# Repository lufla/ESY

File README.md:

# ESY git repository

This repository contains the digital appendix of the ESY project winter term 2025/26.

## Created files:

| Folder | Description |
|--------|-------------|
|[DE10-Nano-CAM](./DE10-Nano-CAM/) | Base board hardware files |
|[firmware/project](./firmware/project/) | Final project files|
|[firmware/hw_simple](./firmware/hw_simple/) | Description of software installation and the complete workflow to create the bitstream |
|[mechanical-design](./mechanical-design/) | 3D files for the mechanical case|
|[Doc](./Doc/) | Source file for the documentation |
|[firmware/hw_test](./firmware/hw_test/) | LED blinky used for all hardware testing |

## Files, that this project is based upon:

| Folder | Description |
|--------|-------------|
|[GateMateCode_Krause](./GateMateCode_Krause/) | Original codebase by Sven Krause adapted to the hardware of this project |
|[ulx5m-gs](./ulx5m-gs/) | SOM board hardware files |
|[Krause_Thesis.pdf](./Krause_Thesis.pdf) | Masters thesis by Sven Krause |

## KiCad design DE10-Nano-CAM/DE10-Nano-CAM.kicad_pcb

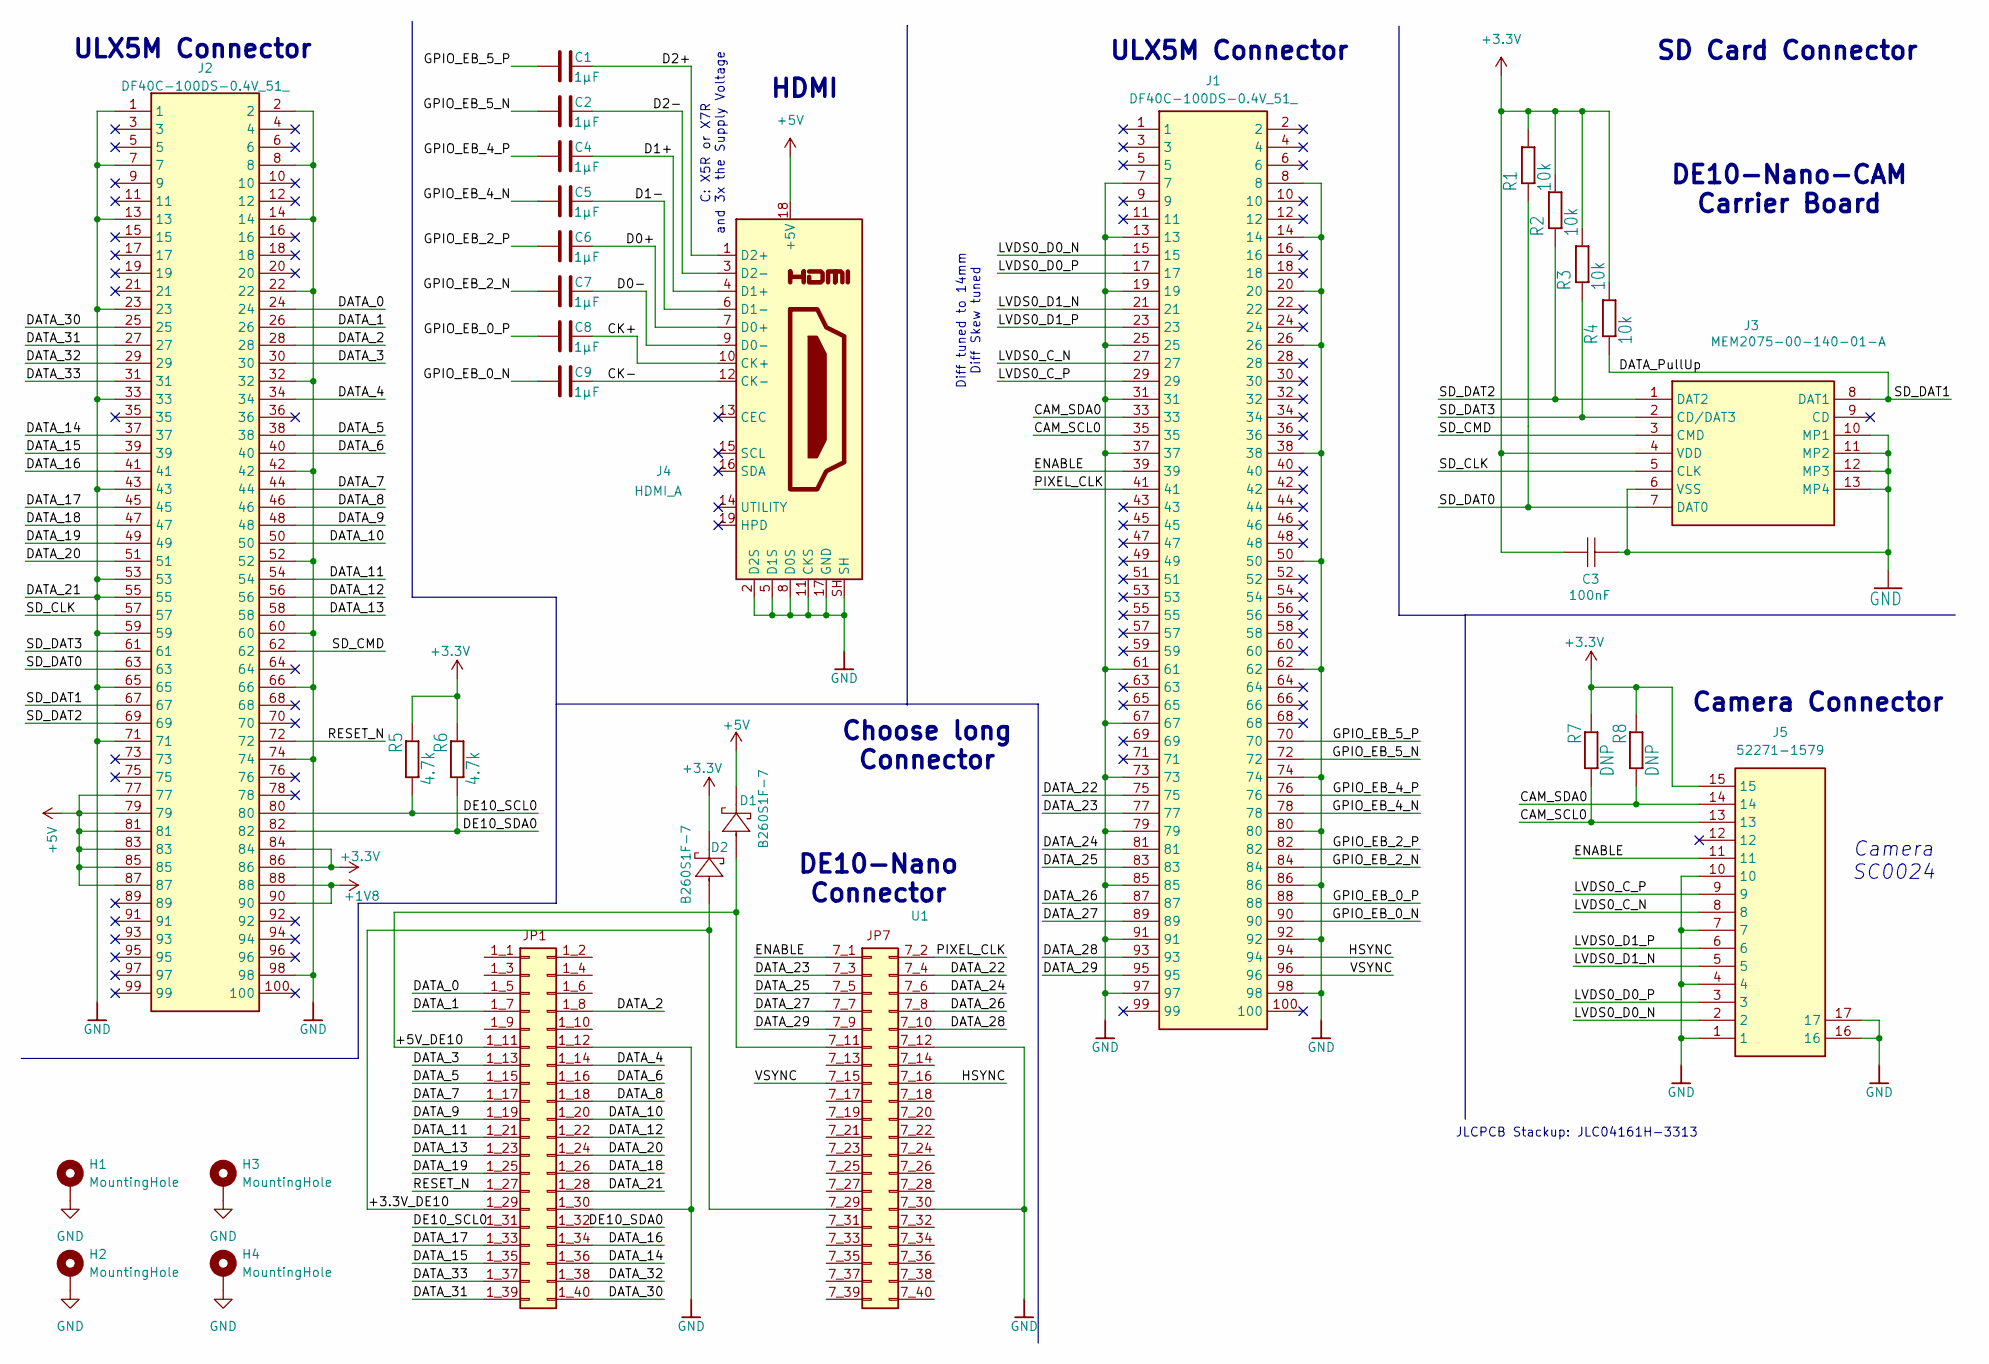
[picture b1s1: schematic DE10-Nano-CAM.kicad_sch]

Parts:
C1, C2, C4, C5, C6, C7, C8, C9: 1µF; C_0402_1005Metric
C3: 100nF; C_0603_1608Metric
D1, D2: B260S1F-7; D_0805_2012Metric; MANUFACTURER_PART_NUMBER B260S1F-7; DIGI-KEY_PART_NUMBER_1 B260S1F-7DITR-ND
H1, H2, H3, H4: MountingHole; MountingHole_2.7mm_M2.5_DIN965_Pad
J1, J2: DF40C-100DS-0.4V_51_; DF40C100DS04V51; Mouser Part Number 798-DF40C100DS0.4V51
J3: MEM2075-00-140-01-A; MEM20750014001A; Mouser Part Number 640-MEM20750014001A
J4: HDMI_A; HDMI_A_Amphenol_10029449-x01xLF_Horizontal
J5: 52271-1579; 522711579; Mouser Part Number 538-52271-1579
R1, R2, R3, R4: 10k; R_0402_1005Metric
R5, R6: 4.7k; R_0603_1608Metric
R7, R8: DNP; R_0603_1608Metric
U1: DE10-Nano

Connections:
+1V8: J2.88, J2.90
+3.3V: C3.2, D2.1, J2.84, J2.86, J3.4 (VDD), J5.15, R1.2, R2.2, R3.2, R4.2, R5.2, R6.2, R7.2, R8.2
+5V: D1.1, J2.77, J2.79, J2.81, J2.83, J2.85, J2.87, J4.18 (+5V)
/+3.3V_DE10: D2.2, U1.1_29, U1.7_29
/+5V_DE10: D1.2, U1.1_11, U1.7_11
/CAM_SCL0: J1.35, J5.13, R7.1
/CAM_SDA0: J1.33, J5.14, R8.1
/CK+: C8.2, J4.10 (CK+)
/CK-: C9.2, J4.12 (CK-)
/D0+: C6.2, J4.7 (D0+)
/D0-: C7.2, J4.9 (D0-)
/D1+: C4.2, J4.4 (D1+)
/D1-: C5.2, J4.6 (D1-)
/D2+: C1.2, J4.1 (D2+)
/D2-: C2.2, J4.3 (D2-)
/DATA_0: J2.24, U1.1_5
/DATA_1: J2.26, U1.1_7
/DATA_2: J2.28, U1.1_8
/DATA_3: J2.30, U1.1_13
/DATA_4: J2.34, U1.1_14
/DATA_5: J2.38, U1.1_15
/DATA_6: J2.40, U1.1_16
/DATA_7: J2.44, U1.1_17
/DATA_8: J2.46, U1.1_18
/DATA_9: J2.48, U1.1_19
/DATA_10: J2.50, U1.1_20
/DATA_11: J2.54, U1.1_21
/DATA_12: J2.56, U1.1_22
/DATA_13: J2.58, U1.1_23
/DATA_14: J2.37, U1.1_36
/DATA_15: J2.39, U1.1_35
/DATA_16: J2.41, U1.1_34
/DATA_17: J2.45, U1.1_33
/DATA_18: J2.47, U1.1_26
/DATA_19: J2.49, U1.1_25
/DATA_20: J2.51, U1.1_24
/DATA_22: J1.75, U1.7_4
/DATA_23: J1.77, U1.7_3
/DATA_24: J1.81, U1.7_6
/DATA_25: J1.83, U1.7_5
/DATA_26: J1.87, U1.7_8
/DATA_27: J1.89, U1.7_7
/DATA_28: J1.93, U1.7_10
/DATA_29: J1.95, U1.7_9
/DATA_30: J2.25, U1.1_40
/DATA_31: J2.27, U1.1_39
/DATA_32: J2.29, U1.1_38
/DATA_33: J2.31, U1.1_37
/DATA_PullUp: J2.67, J3.8 (DAT1), R4.1
/DE10_SCL0: J2.80, R5.1, U1.1_31
/DE10_SDA0: J2.82, R6.1, U1.1_32
/ENABLE: J1.39, J5.11, U1.7_1
/GPIO_EB_0_N: C9.1, J1.90
/GPIO_EB_0_P: C8.1, J1.88
/GPIO_EB_2_N: C7.1, J1.84
/GPIO_EB_2_P: C6.1, J1.82
/GPIO_EB_4_N: C5.1, J1.78
/GPIO_EB_4_P: C4.1, J1.76
/GPIO_EB_5_N: C2.1, J1.72
/GPIO_EB_5_P: C1.1, J1.70
/HSYNC: J1.94, U1.7_16
/LVDS0_C_N: J1.27, J5.8
/LVDS0_C_P: J1.29, J5.9
/LVDS0_D0_N: J1.15, J5.2
/LVDS0_D0_P: J1.17, J5.3
/LVDS0_D1_N: J1.21, J5.5
/LVDS0_D1_P: J1.23, J5.6
/PIXEL_CLK: J1.41, U1.7_2
/RESET_N: J2.72, U1.1_27
/SD_CLK: J2.57, J3.5 (CLK)
/SD_CMD: J2.62, J3.3 (CMD)
/SD_DAT0: J2.63, J3.7 (DAT0), R1.1
/SD_DAT2: J2.69, J3.1 (DAT2), R2.1
/SD_DAT3: J2.61, J3.2 (CD/DAT3), R3.1
/VSYNC: J1.96, U1.7_15
GND: C3.1, H1.1, H2.1, H3.1, H4.1, J1.7, J1.8, J1.13, J1.14, J1.19, J1.20, J1.25, J1.26, J1.31, J1.37, J1.38, J1.50, J1.61, J1.62, J1.67, J1.73, J1.74, J1.79, J1.80, J1.85, J1.86, J1.91, J1.92, J1.97, J1.98, J2.1, J2.2, J2.7, J2.8, J2.13, J2.14, J2.22, J2.23, J2.32, J2.33, J2.42, J2.43, J2.52, J2.53, J2.55, J2.59, J2.60, J2.65, J2.66, J2.71, J2.74, J2.98, J3.6 (VSS), J3.10 (MP1), J3.11 (MP2), J3.12 (MP3), J3.13 (MP4), J4.2 (D2S), J4.5 (D1S), J4.8 (D0S), J4.11 (CKS), J4.17 (GND), J4.SH, J5.1, J5.4, J5.7, J5.10, J5.16, J5.17, U1.1_12, U1.1_28, U1.1_30, U1.7_12, U1.7_30

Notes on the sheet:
DE10-Nano-CAM Carrier Board
Camera SC0024
C: X5R or X7R and 3x the Supply Voltage
Camera Connector
Choose long Connector
DE10-Nano Connector
JLCPCB Stackup: JLC04161H-3313
ULX5M Connector
SD Card Connector
HDMI
Diff tuned to 14mm Diff Skew tuned

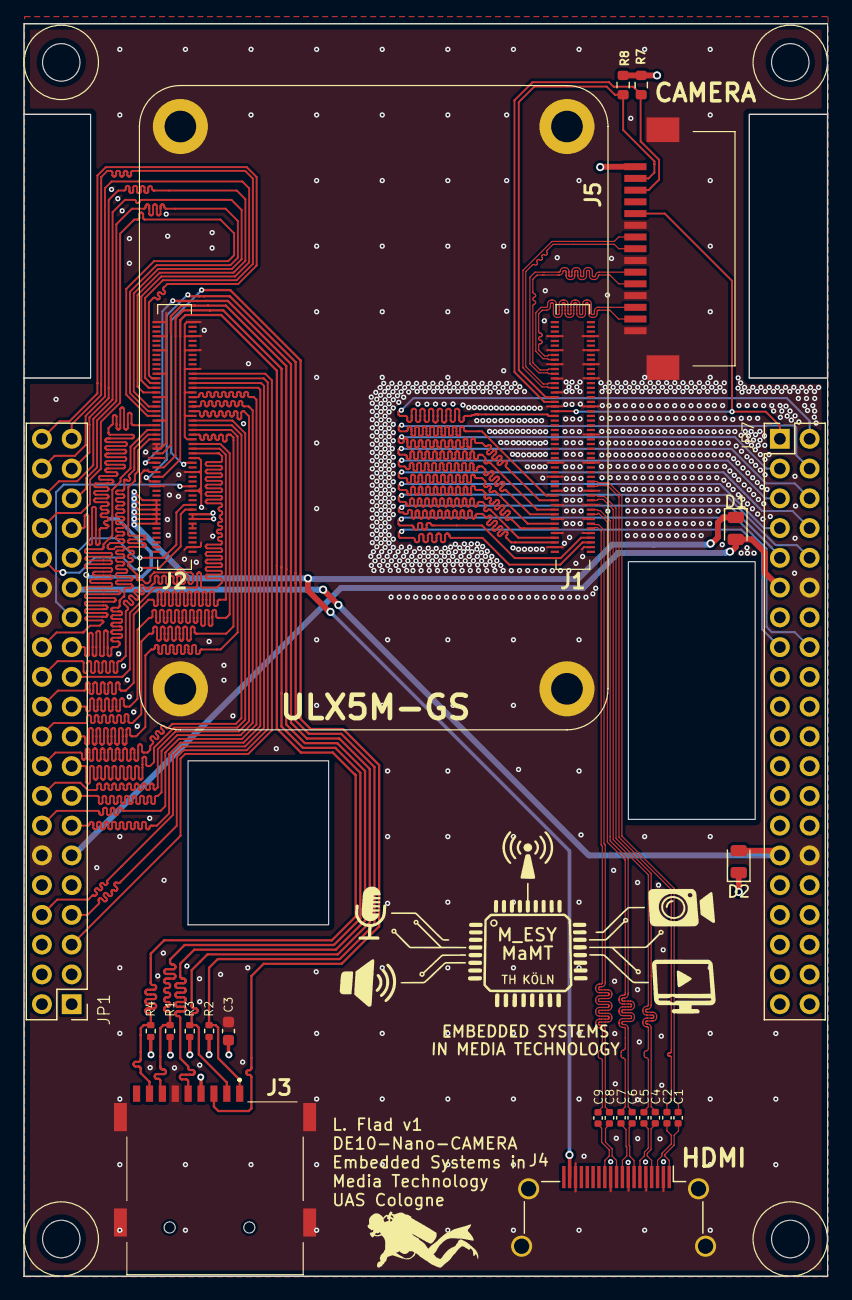
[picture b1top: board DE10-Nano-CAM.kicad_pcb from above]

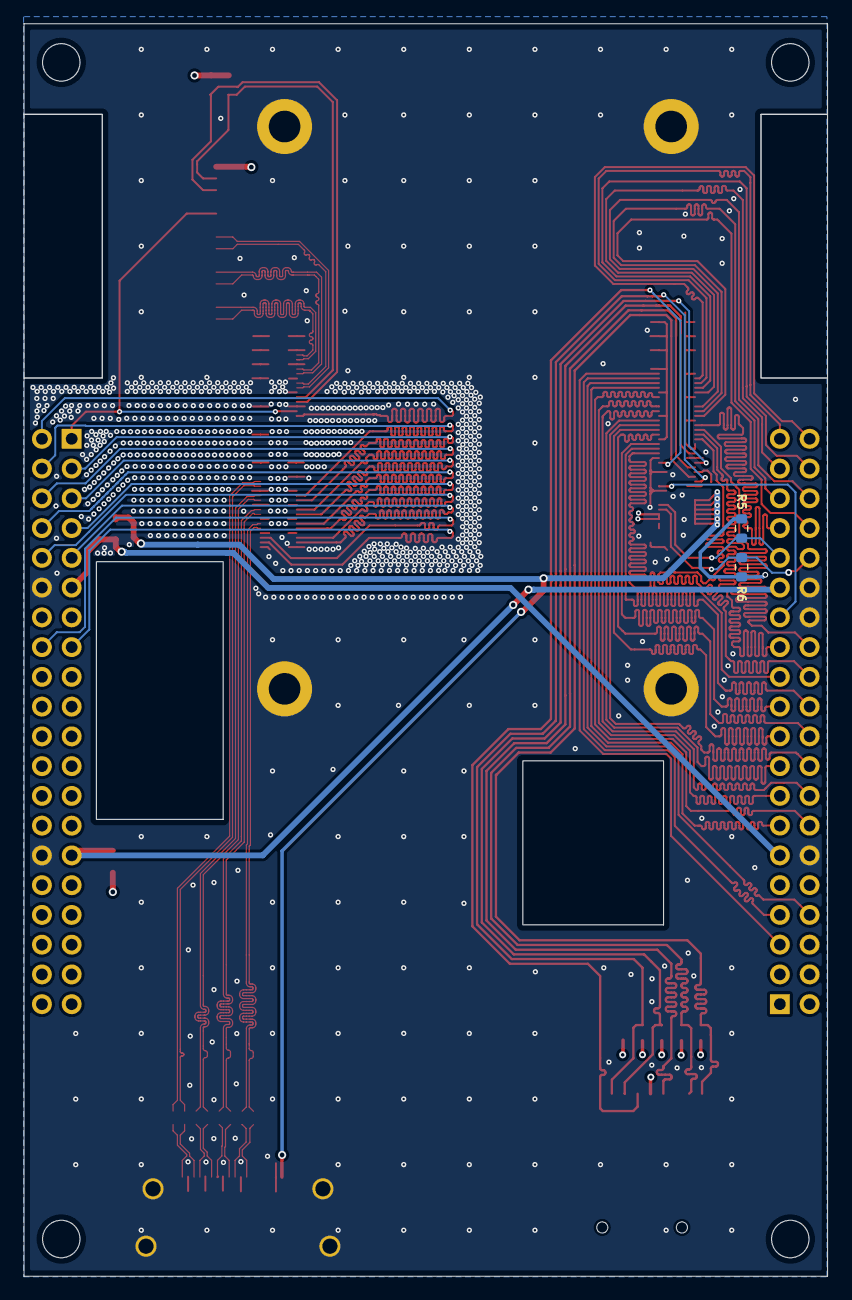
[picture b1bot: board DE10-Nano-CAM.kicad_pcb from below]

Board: 4 copper layers, 68.6 x 106.9 mm, 29 parts (2 on the bottom side), 76 nets.

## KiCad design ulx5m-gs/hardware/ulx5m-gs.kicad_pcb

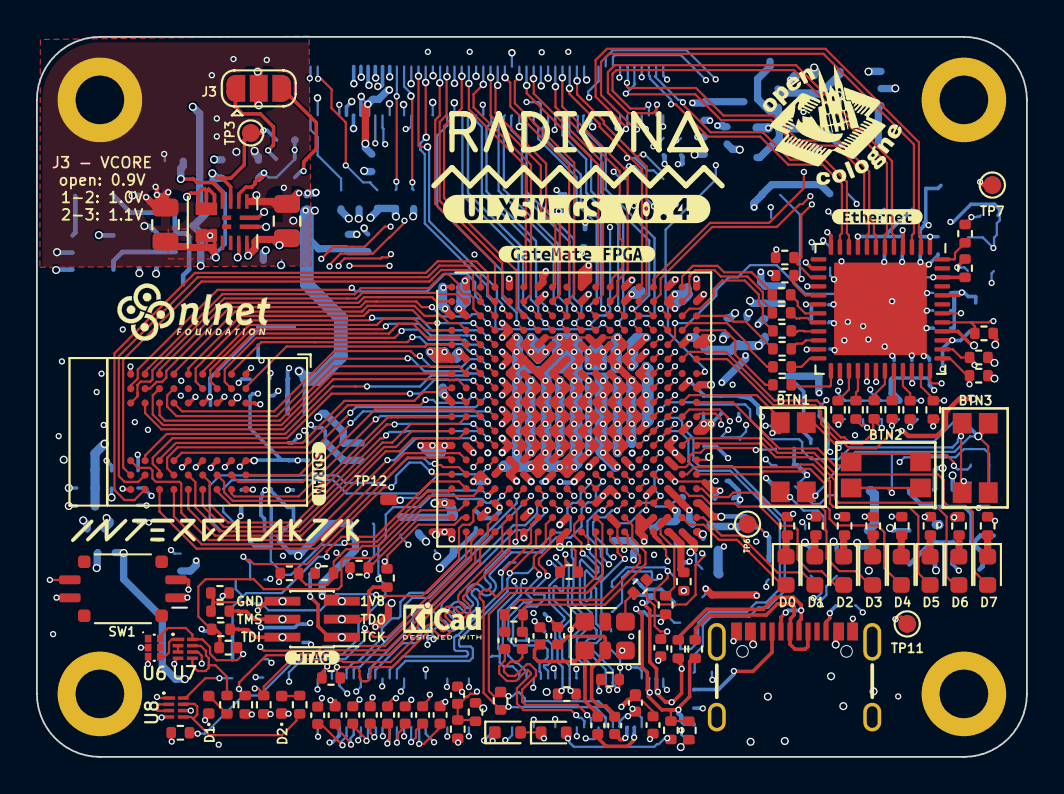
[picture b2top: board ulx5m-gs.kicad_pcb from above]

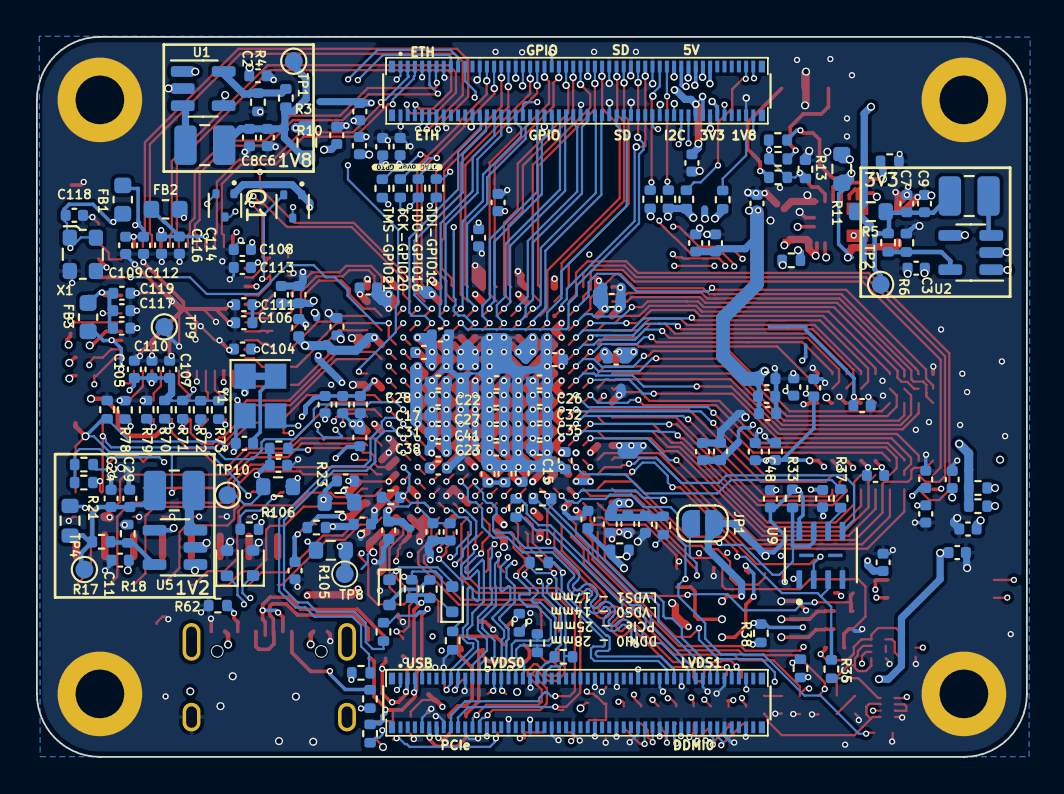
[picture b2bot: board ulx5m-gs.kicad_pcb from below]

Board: 6 copper layers, 55.0 x 40.0 mm, 310 parts (192 on the bottom side), 275 nets.

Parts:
BTN1, BTN2, BTN3: SW_Push; Switch_EVPAA
C1, C10: 22u; C_0805_2012Metric
C2, C3, C11, C115: 4u7; C_0402_1005Metric
C4, C15, C18, C23, C28, C32, C35, C38, C41, C110, C111, C113, C119, C126: 10n; C_0402_1005Metric
C6, C7, C24, C104, C105, C109, C114: 10u; C_0402_1005Metric
C8, C9, C29: 1u; C_0402_1005Metric
C13, C16, C21, C26, C36, C44, C51, C54, C75, C78, C86, C90, C94, C100, C122, C123, C131: 2u2; C_0402_1005Metric
C14, C17, C22, C27, C31, C34, C37, C40, C42, C45, C47, C48, C49, C52, C55, C56, C57, C76, C79, C80, C88, C89, C92, C93, C96, C97, C102, C103, C106, C107, C108, C112, C116, C117, C118, C127, C128, C129, C130, C132, C133, C134, C135, C136, C137, C138: 100n; C_0402_1005Metric
C33, C59, C60, C61, C62, C63, C64, C65, C66, C87, C91, C95, C120, C121: 220n; C_0402_1005Metric
C39, C43, C50, C53, C58, C77, C98, C124, C125: 22u; C_0402_1005Metric
C85: 2.2uF; C_0402_1005Metric
C99, C101, C140, C141: 22nF; C_0402_1005Metric
D1: green; D_0402_1005Metric
D2: red; D_0402_1005Metric
D3, D4: 3.6V; D_SOD-523
D5, D6, D7, D8: 1N914; D_SOD-523
D9, D10, D11, D12, D13, D14, D15, D16: LED; LED_0603_1608Metric
FB1, FB2, FB3: BLM18PG121SN1D; L_0603_1608Metric
H1, H2, H3, H4: MountingHole; MountingHole_2.7mm_M2.5_DIN965_Pad
J1, J2: DF40C-100DP-0.4V_51_; HRS_DF40C-100DP-0.4V_51_
J3: Vcore_sel; SolderJumper-3_P1.3mm_Open_RoundedPad1.0x1.5mm
J4: JTAG; PinHeader_2x03_P1.00mm_Vertical_SMD
J5: USB_C_Receptacle; USB-C_16
JP1: POR_EN; SolderJumper-2_P1.3mm_Open_RoundedPad1.0x1.5mm
L1, L2, L3: DFE322512F-2R2M=P2; L_1008_2520Metric
LoGo_opencologne: MountingHole; open_cologne_small
Q1, Q2: BSS138; SOT-523
R1, R4, R5, R143: 100k; R_0402_1005Metric
R2: 51k; R_0402_1005Metric
R3, R17, R18: 200k; R_0402_1005Metric
R6: 22k; R_0402_1005Metric
R7, R8, R116, R141, R142: 0R; R_0402_1005Metric
R9, R107, R108, R110, R112, R113, R115: dnp; R_0402_1005Metric
R10, R11, R13, R21: 0R; R_0603_1608Metric
R12: 40k; R_0402_1005Metric
R14: 120k; R_0402_1005Metric
R15: 20k; R_0402_1005Metric
R16: 60k; R_0402_1005Metric
R23, R105, R106: 1R; R_0603_1608Metric
R24, R25, R27, R29, R30, R111, R128, R134, R138, R139, R147, R148, R149, R150: 10k; R_0402_1005Metric
R31, R32: 200R; R_0402_1005Metric
R33, R34, R35, R36, R38, R39, R66, R67, R70, R71, R72, R73, R78, R79, R84, R85, R96: 4k7; R_0402_1005Metric
R37, R40, R41, R42, R43, R89, R90, R91, R92, R93, R94, R97, R98, R99, R100, R101, R102, R104: 27R; R_0402_1005Metric
R44, R45: 27; R_0402_1005Metric
R46, R48, R58: 1k; R_0402_1005Metric
R47, R55, R103: 12k1; R_0402_1005Metric
R50, R51, R54, R129, R130, R131, R132, R135, R136: 150R; R_0402_1005Metric
R59, R63, R64, R65, R86, R87, R88, R95, R118: R300; R_0402_1005Metric
R61, R62: 5k1; R_0402_1005Metric
R109: 200; R_0402_1005Metric
R121, R122, R123: 4R7; R_0402_1005Metric
R144, R145, R146: 1K; R_0402_1005Metric
SW1: 219-2MST; SW_DIP_SPSTx02_Slide_Copal_CVS-02xB_W5.9mm_P1mm
TP1: 1V8; TestPoint_Pad_D1.0mm
TP2: 3V3; TestPoint_Pad_D1.0mm
TP3: Vcore; TestPoint_Pad_D1.0mm
TP4: 1V2; TestPoint_Pad_D1.0mm
TP6: VDD_PLL; TestPoint_Pad_D1.0mm
TP7, TP9, TP11: GND; TestPoint_Pad_D1.0mm
TP8: VDD_SER_PLL; TestPoint_Pad_D1.0mm
TP10: VDD_SER; TestPoint_Pad_D1.0mm
TP12: SPI_FWD; TestPoint_Pad_1.0x1.0mm
U1, U2, U5: TLV62569DBV; SOT-23-5
U3: MPM3833CGRH-Z
U4: GateMate-CCGM1A1; BGA-324_15.0x15.0mm_Layout18x18_P0.8mm_Ball0.45mm_Pad0.4mm_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
U6: 74LVC1G04GM,115; PESD3V3L5UF115
U7, U8: 74LVC2G00HK3-7; 74LVC2G00HK37
U9: AT25QL321-MBUE-T; SON80P400X300X60-10N
U10: IS42S16320D-6BLI
U14: KSZ9031RNXCA; QFN-48-1EP_7x7mm_P0.5mm_EP5.15x5.15mm
X1: ECS-2520MV-250-xx; Oscillator_SMD_ECS_2520MV-xxx-xx-4Pin_2.5x2.0mm
X2: 511FCA100M000BAG; Oscillator_SMD_SiTime_PQFD-6L_3.2x2.5mm
Y1: ASE2-25.000MHZ-L-C-T; Crystal_SMD_TXC_7M-4Pin_3.2x2.5mm
kibuzzard-68DC261C: G***; kibuzzard-68DC261C
kibuzzard-686AA7AF: G***; kibuzzard-686AA7AF
kibuzzard-686AA8CB: G***; kibuzzard-686AA8CB
kibuzzard-686AA726: G***; kibuzzard-686AA726
kibuzzard-686CE423: G***; kibuzzard-686CE423
kibuzzard-689F41CF: G***; kibuzzard-689F41CF
radiona: radiona

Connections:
+1V2: C49.1, C104.1, C106.1, C108.1, C111.1, C113.1, FB2.1, FB3.1, R21.2, R121.1, U14.14 (DVDDL), U14.18 (DVDDL), U14.23 (DVDDL), U14.26 (DVDDL), U14.30 (DVDDL), U14.39 (DVDDL)
+3V3: C85.1, C94.1, C95.1, C96.1, C97.1, C99.1, C101.1, C118.1, C140.1, C141.1, FB1.2, J2.84, J2.86, R11.2, R58.2, R115.2, R128.1, R134.1, R138.1, R139.2, U4.G14 (VDD_EA), U4.H17 (VDD_EA), U4.J14 (VDD_EA), U4.L14 (VDD_EA), U4.L17 (VDD_EA), X1.1 (Tri-State), X1.4 (VDD)
+5V: C1.1, C2.1, C3.1, C11.1, J2.77, J2.79, J2.81, J2.83, J2.85, J2.87, J5.VBUS, R1.1, U1.1 (EN), U1.4 (VIN), U2.1 (EN), U2.4 (VIN), U3.13 (IN), U3.14 (IN), U5.1 (EN), U5.4 (VIN)
/cm4-gpio/ETH0_LEDG: J2.15, Q2.3 (D)
/cm4-gpio/ETH0_LEDY: J2.17, Q1.3 (D)
/cm4-gpio/ETH0_N: J2.10, U14.3 (TXRXM_A)
/cm4-gpio/ETH0_P: J2.12, U14.2 (TXRXP_A)
/cm4-gpio/ETH1_N: J2.6, U14.6 (TXRXM_B)
/cm4-gpio/ETH1_P: J2.4, U14.5 (TXRXP_B)
/cm4-gpio/ETH2_N: J2.9, U14.8 (TXRXM_C)
/cm4-gpio/ETH2_P: J2.11, U14.7 (TXRXP_C)
/cm4-gpio/ETH3_N: J2.5, U14.11 (TXRXM_D)
/cm4-gpio/ETH3_P: J2.3, U14.10 (TXRXP_D)
/cm4-gpio/FAN_PWM: J2.19, U4.D11 (IO_NB_A3)
/cm4-gpio/GPIO2: J2.58, U4.D7 (IO_NA_B5)
/cm4-gpio/GPIO3: J2.56, U4.C7 (IO_NA_A5)
/cm4-gpio/GPIO4: J2.54, U4.D8 (IO_NA_B6)
/cm4-gpio/GPIO5: J2.34, U4.C12 (IO_NB_B5)
/cm4-gpio/GPIO6: J2.30, U4.C13 (IO_NB_B6)
/cm4-gpio/GPIO7: J2.37, U4.B11 (IO_NB_A2)
/cm4-gpio/GPIO8: J2.39, U4.A11 (IO_NB_B2)
/cm4-gpio/GPIO9: J2.40, U4.D10 (IO_NB_A1)
/cm4-gpio/GPIO10: J2.44, U4.C10 (IO_NB_B1)
/cm4-gpio/GPIO11: J2.38, U4.C11 (IO_NB_B3)
/cm4-gpio/GPIO12: J2.31, R147.1, U4.A12 (IO_NB_B4)
/cm4-gpio/GPIO13: J2.28, U4.D13 (IO_NB_A6)
/cm4-gpio/GPIO14: J2.55, U4.A6 (IO_NA_A4)
/cm4-gpio/GPIO15: J2.51, U4.B6 (IO_NA_B4)
/cm4-gpio/GPIO16: J2.29, R148.1, U4.B12 (IO_NB_A4)
/cm4-gpio/GPIO17: J2.50, U4.C8 (IO_NA_A6)
/cm4-gpio/GPIO18: J2.49, U4.A8 (IO_NA_A7)
/cm4-gpio/GPIO19: J2.26, U4.C14 (IO_NB_B8)
/cm4-gpio/GPIO20: J2.27, R149.1, U4.A14 (IO_NB_B7)
/cm4-gpio/GPIO21: J2.25, R150.1, U4.B14 (IO_NB_A7)
/cm4-gpio/GPIO22: J2.46, U4.D9 (IO_NA_B8)
/cm4-gpio/GPIO23: J2.47, U4.B8 (IO_NA_B7)
/cm4-gpio/GPIO24: J2.45, U4.A9 (IO_NB_B0)
/cm4-gpio/GPIO25: J2.41, U4.B9 (IO_NB_A0)
/cm4-gpio/GPIO26: J2.24, U4.D14 (IO_NB_A8)
/cm4-gpio/GPIO27: J2.48, U4.C9 (IO_NA_A8)
/cm4-gpio/ID_SC: J2.35, U4.H15 (IO_EA_B6)
/cm4-gpio/ID_SD: J2.36, U4.H16 (IO_EA_A6)
/cm4-gpio/SCL0: J2.80, U4.J15 (IO_EA_B5)
/cm4-gpio/SDA0: J2.82, U4.J16 (IO_EA_A5)
/cm4-gpio/SD_CLK: J2.57, U4.C6 (IO_NA_A3)
/cm4-gpio/SD_CMD: J2.62, U4.D6 (IO_NA_B3)
/cm4-gpio/SD_DAT0: J2.63, U4.A4 (IO_NA_A1)
/cm4-gpio/SD_DAT1: J2.67, U4.D12 (IO_NB_A5)
/cm4-gpio/SD_DAT2: J2.69, U4.C5 (IO_NA_B2)
/cm4-gpio/SD_DAT3: J2.61, U4.B5 (IO_NA_A2)
/cm4-gpio/USB_CC1: J5.A5 (CC1), R61.2
/cm4-gpio/USB_CC2: J5.B5 (CC2), R62.2
/cm4-hsio/DDMI0_CLK_N: C66.1, J1.90
/cm4-hsio/DDMI0_CLK_P: C65.1, J1.88
/cm4-hsio/DDMI0_TX0_N: C60.1, J1.84
/cm4-hsio/DDMI0_TX0_P: C59.1, J1.82
/cm4-hsio/DDMI0_TX1_N: C62.1, J1.78
/cm4-hsio/DDMI0_TX1_P: C61.1, J1.76
/cm4-hsio/DDMI0_TX2_N: C64.1, J1.72
/cm4-hsio/DDMI0_TX2_P: C63.1, J1.70
/cm4-hsio/LVDS0_C_N: J1.27, R50.2, U4.T9 (IO_SA_B6)
/cm4-hsio/LVDS0_C_P: J1.29, R50.1, U4.R9 (IO_SA_A6)
/cm4-hsio/LVDS0_D0_N: J1.15, R51.2, U4.V10 (IO_SA_B8)
/cm4-hsio/LVDS0_D0_P: J1.17, R51.1, U4.U10 (IO_SA_A8)
/cm4-hsio/LVDS0_D1_N: J1.21, R54.2, U4.T10 (IO_SA_B7)
/cm4-hsio/LVDS0_D1_P: J1.23, R54.1, U4.R10 (IO_SA_A7)
/cm4-hsio/LVDS0_D2_N: J1.33, R130.2, U4.V8 (IO_SA_B5)
/cm4-hsio/LVDS0_D2_P: J1.35, R130.1, U4.U8 (IO_SA_A5)
/cm4-hsio/LVDS0_D3_N: J1.39, R131.2, U4.T8 (IO_SA_B4)
/cm4-hsio/LVDS0_D3_P: J1.41, R131.1, U4.R8 (IO_SA_A4)
/cm4-hsio/LVDS1_C_N: J1.87, R129.2, U4.T6 (IO_SA_B1)
/cm4-hsio/LVDS1_C_P: J1.89, R129.1, U4.R6 (IO_SA_A1)
/cm4-hsio/LVDS1_D0_N: J1.75, R132.2, U4.V7 (IO_SA_B3)
/cm4-hsio/LVDS1_D0_P: J1.77, R132.1, U4.U7 (IO_SA_A3)
/cm4-hsio/LVDS1_D1_N: J1.81, R135.2, U4.T7 (IO_SA_B2)
/cm4-hsio/LVDS1_D1_P: J1.83, R135.1, U4.R7 (IO_SA_A2)
/cm4-hsio/LVDS1_D2_N: J1.93, R136.2, U4.V5 (IO_SA_B0)
/cm4-hsio/LVDS1_D2_P: J1.95, R136.1, U4.U5 (IO_SA_A0)
/cm4-hsio/PCIe_CLK_N: C137.2, J1.12
/cm4-hsio/PCIe_CLK_P: C136.2, J1.10
/cm4-hsio/PCIe_RX_N: J1.18, R107.2, U4.V11 (SER_RX_N)
/cm4-hsio/PCIe_RX_P: J1.16, R107.1, U4.U11 (SER_RX_P)
/cm4-hsio/PCIe_TX_N: C135.2, J1.24
/cm4-hsio/PCIe_TX_P: C134.2, J1.22
/cm4-hsio/USB_N: D4.1 (K), J1.3, R44.1, R48.1, R55.2, R141.2
/cm4-hsio/USB_OTG_ID: J1.1, U4.K16 (IO_EA_A3)
/cm4-hsio/USB_P: D3.1 (K), J1.5, R45.1, R46.2, R47.2, R58.1, R142.2
/config/+1V8_FLASH: C43.1, C44.1, C45.1, R123.1, U4.N5 (VDD_WA), U4.P3 (VDD_WA), U4.P5 (VDD_WA), U4.T1 (VDD_WA), U4.U3 (VDD_WA)
/config/CFG_DONE: U4.V3 (IO_WA_B2/CFG_DONE), U6.2 (A)
/config/JTAG_CFG_MD0: R29.1, U4.R5 (CFG_MD0/IO_WA_A0)
/config/JTAG_CFG_MD1: R27.1, U4.T5 (CFG_MD1/IO_WA_B0)
/config/JTAG_CFG_MD2: R25.1, SW1.4, U4.U4 (CFG_MD2/IO_WA_A1)
/config/JTAG_CFG_MD3: R24.1, SW1.3, U4.V4 (CFG_MD3/IO_WA_B1)
/config/JTAG_POR: JP1.2 (B), R30.1, U4.U1 (POR_EN/IO_WA_A3)
/config/JTAG_TCK: R39.1, R40.1, R149.2, U4.R3 (JTAG_TCK/IO_WA_A5)
/config/JTAG_TDI: R36.2, R41.1, R147.2, U4.T2 (JTAG_TDI/IO_WA_A4)
/config/JTAG_TDO: R42.1, R148.2, U4.U2 (JTAG_TDO/IO_WA_B3)
/config/JTAG_TMS: R34.2, R43.1, R150.2, U4.T3 (JTAG_TMS/IO_WA_B4)
/config/SPI_CSN: R38.2, U4.N3 (IO_WA_A8/~SPI_CS), U9.1 (~CS)
/config/SPI_IO0: U4.P2 (IO_WA_B7/SPI_D0), U9.5 (SI/SIO0)
/config/SPI_IO1: U4.P1 (IO_WA_A7/SPI_D1), U9.2 (SO/SIO1)
/config/SPI_IO2: R35.2, U4.R2 (IO_WA_B6/SPI_D2), U9.3 (~WP/SIO2)
/config/SPI_IO3: R33.2, U4.R1 (IO_WA_A6/SPI_D3), U9.7 (~RESET/SIO3)
/config/SPI_SCK: R37.1, U4.N4 (IO_WA_B8/SPI_CLK)
/config/~CFG_FAIL: U4.V2 (IO_WA_A2/~CFG_FAILED), U8.1 (1A)
/ethernet/BTN1: BTN1.2, R144.2, U4.J17 (IO_EA_B4)
/ethernet/BTN2: BTN2.2, R145.2, U4.J18 (IO_EA_A4)
/ethernet/BTN3: BTN3.2, R146.2, U4.K15 (IO_EA_B3)
/ethernet/ETH_CLK: R104.2, U4.E16 (IO_EB_A3), U14.46 (XI)
/ethernet/FPD1+: J5.A6 (D+), J5.B6 (D+), R45.2
/ethernet/FPD1-: J5.A7 (D-), J5.B7 (D-), R44.2
/ethernet/LEDG: Q2.2 (S), R85.1, U14.17 (LED1/PHAD0/PME_N1)
/ethernet/LEDY: Q1.2 (S), R84.1, U14.15 (LED2/PHYAD1)
/ethernet/PHY_CLK: R104.1, X1.3 (OUT)
/ethernet/RGMII_INT_N: R67.2, U4.C15 (IO_EB_B7), U14.38 (INT_N/PME_N2)
/ethernet/RGMII_MDC: U4.C16 (IO_EB_B6), U14.36 (MDC)
/ethernet/RGMII_MDIO: R96.2, U4.D16 (IO_EB_A6), U14.37 (MDIO)
/ethernet/RGMII_REFCLK: R66.2, U4.A15 (IO_EB_B8), U14.41 (CLK125_NDO/LED_MODE)
/ethernet/RGMII_RST_N: U4.E15 (IO_EB_B3), U14.42 (RESET_N)
/ethernet/RGMII_RX0: R98.1, U14.32 (RXD0/MODE0)
/ethernet/RGMII_RX1: R99.1, U14.31 (RXD1/MODE1)
/ethernet/RGMII_RX2: R100.1, U14.28 (RXD2/MODE2)
/ethernet/RGMII_RX3: R101.1, U14.27 (RXD3/MODE3)
/ethernet/RGMII_RXD0: R70.2, R98.2, U4.F18 (IO_EB_A0)
/ethernet/RGMII_RXD1: R71.2, R99.2, U4.F17 (IO_EB_B0)
/ethernet/RGMII_RXD2: R72.2, R100.2, U4.F16 (IO_EB_A1)
/ethernet/RGMII_RXD3: R73.2, R101.2, U4.F15 (IO_EB_B1)
/ethernet/RGMII_RX_CK: R102.1, U14.35 (RX_CLK/PHYAD2)
/ethernet/RGMII_RX_CLK: R78.1, R102.2, U4.D15 (IO_EB_A7)
/ethernet/RGMII_RX_D: R97.1, U14.33 (RX_DV/CLK125_EN)
/ethernet/RGMII_RX_DV: R79.1, R97.2, U4.B15 (IO_EB_A8)
/ethernet/RGMII_TX0: R89.2, U4.A17 (IO_EB_B5)
/ethernet/RGMII_TX1: R90.2, U4.B17 (IO_EB_A5)
/ethernet/RGMII_TX2: R91.2, U4.C17 (IO_EB_B4)
/ethernet/RGMII_TX3: R92.2, U4.C18 (IO_EB_A4)
/ethernet/RGMII_TXD0: R89.1, U14.19 (TXD0)
/ethernet/RGMII_TXD1: R90.1, U14.20 (TXD1)
/ethernet/RGMII_TXD2: R91.1, U14.21 (TXD2)
/ethernet/RGMII_TXD3: R92.1, U14.22 (TXD3)
/ethernet/RGMII_TXE: R93.2, U4.D18 (IO_EB_A2)
/ethernet/RGMII_TXEN: R93.1, U14.25 (TX_EN)
/ethernet/RGMII_TX_CK: R94.2, U4.D17 (IO_EB_B2)
/ethernet/RGMII_TX_CLK: R94.1, U14.24 (GTX_CLK)
/ethernet/USB25_N: R141.1, U4.L15 (IO_EA_B1), U4.M14 (IO_EA_B0)
/ethernet/USB25_P: R142.1, U4.L16 (IO_EA_A1), U4.M15 (IO_EA_A0)
/ethernet/USB_PULL_N: D7.2 (A), D8.1 (K), U4.K17 (IO_EA_B2)
/ethernet/USB_PULL_P: D5.2 (A), D6.1 (K), U4.K18 (IO_EA_A2)
/lvds/+1V2_SA: C50.1, C51.1, C52.1, R121.2, U4.P6 (VDD_SA), U4.P8 (VDD_SA), U4.P10 (VDD_SA), U4.U6 (VDD_SA), U4.U9 (VDD_SA)
/lvds/+1V8_SB: C53.1, C54.1, C55.1, R122.1, U4.N11 (VDD_SB), U4.N13 (VDD_SB), U4.N18 (VDD_SB), U4.R15 (VDD_SB), U4.T18 (VDD_SB)
/lvds/ALED0: D9.1 (K), R59.1
/lvds/ALED1: D10.1 (K), R63.1
/lvds/ALED2: D11.1 (K), R64.1
/lvds/ALED3: D12.1 (K), R65.1
/lvds/ALED4: D13.1 (K), R86.1
/lvds/ALED5: D14.1 (K), R87.1
/lvds/ALED6: D15.1 (K), R88.1
/lvds/ALED7: D16.1 (K), R95.1
/lvds/CLK_25MHz: U4.N14 (CLK0/IO_SB_A8), Y1.3
/lvds/DDMI0_HS_CLK_N: C66.2, U4.P13 (IO_SB_B7)
/lvds/DDMI0_HS_CLK_P: C65.2, U4.P12 (CLK1/IO_SB_A7)
/lvds/DDMI0_HS_TX0_N: C60.2, U4.R11 (IO_SB_B4)
/lvds/DDMI0_HS_TX0_P: C59.2, U4.P11 (IO_SB_A4)
/lvds/DDMI0_HS_TX1_N: C62.2, U4.R14 (IO_SB_B5)
/lvds/DDMI0_HS_TX1_P: C61.2, U4.R13 (CLK3/IO_SB_A5)
/lvds/DDMI0_HS_TX2_N: C64.2, U4.P15 (IO_SB_B6)
/lvds/DDMI0_HS_TX2_P: C63.2, U4.P14 (CLK2/IO_SB_A6)
/lvds/LED0: D9.2 (A), U4.U17 (IO_SB_A0)
/lvds/LED1: D10.2 (A), U4.U18 (IO_SB_B0)
/lvds/LED2: D11.2 (A), U4.R17 (IO_SB_A1)
/lvds/LED3: D12.2 (A), U4.R18 (IO_SB_B1)
/lvds/LED4: D13.2 (A), U4.P18 (IO_SB_B2)
/lvds/LED5: D14.2 (A), U4.P17 (IO_SB_A2)
/lvds/LED6: D15.2 (A), U4.M18 (IO_SB_B3)
/lvds/LED7: D16.2 (A), U4.M17 (IO_SB_A3)
/serdes/PCIe_TX_BC_N: C135.1, R110.2, U4.V13 (SER_TX_N)
/serdes/PCIe_TX_BC_P: C134.1, R110.1, U4.U13 (SER_TX_P)
/serdes/SER_CK_N: C130.2, R108.2, U4.T13 (SER_CLK_N)
/serdes/SER_CK_P: C129.2, R108.1, U4.T12 (SER_CLK)
/serdes/SER_CLK_N: C130.1, C137.1, X2.5 (OUT-)
/serdes/SER_CLK_P: C129.1, C136.1, X2.4 (OUT+)
/serdes/SER_PORT_ADJ: C133.1, R112.2, R113.1, U4.V15 (POR_ADJ)
GND: C1.2, C2.2, C3.2, C4.1, C6.2, C7.2, C8.2, C9.2, C10.2, C11.2, C13.2, C14.2, C15.2, C16.2, C17.2, C18.2, C21.2, C22.2, C23.2, C24.2, C26.2, C27.2, C28.2, C29.2, C31.2, C32.2, C33.2, C34.2, C35.2, C36.2, C37.2, C38.2, C39.2, C40.2, C41.2, C42.2, C43.2, C44.2, C45.2, C47.2, C48.2, C49.2, C50.2, C51.2, C52.2, C53.2, C54.2, C55.2, C56.2, C57.2, C58.2, C75.2, C76.2, C77.2, C78.2, C79.2, C80.2, C85.2, C86.2, C87.2, C88.2, C89.2, C90.2, C91.2, C92.2, C93.2, C94.2, C95.2, C96.2, C97.2, C98.2, C99.2, C100.2, C101.2, C102.2, C103.2, C104.2, C105.2, C106.2, C107.2, C108.2, C109.2, C110.2, C111.2, C112.2, C113.2, C114.2, C115.2, C116.2, C117.2, C118.2, C119.2, C120.2, C121.2, C122.2, C123.2, C124.2, C125.2, C126.2, C127.2, C128.2, C131.2, C132.2, C133.2, C138.2, C140.2, C141.2, D1.1 (K), D2.1 (K), D3.2 (A), D4.2 (A), H1.1, H2.1, H3.1, H4.1, J1.7, J1.8, J1.13, J1.14, J1.19, J1.20, J1.25, J1.26, J1.31, J1.32, J1.37, J1.38, J1.44, J1.50, J1.55, J1.56, J1.61, J1.62, J1.67, J1.68, J1.73, J1.74, J1.79, J1.80, J1.85, J1.86, J1.91, J1.92, J1.97, J1.98, J2.1, J2.2, J2.7, J2.8, J2.13, J2.14, J2.22, J2.23, J2.32, J2.33, J2.42, J2.43, J2.52, J2.53, J2.59, J2.60, J2.65, J2.66, J2.71, J2.74, J2.98, J3.2, J4.6, J5.GND, J5.S (SHIELD), R2.2, R4.2, R6.2, R7.2, R8.2, R12.1, R18.2, R24.2, R25.2, R27.2, R29.2, R30.2, R39.2, R59.2, R61.1, R62.1, R63.2, R64.2, R65.2, R78.2, R79.2, R84.2, R85.2, R86.2, R87.2, R88.2, R95.2, R103.1, R109.1, R113.2, R118.2, TP7.1, TP9.1, TP11.1, U1.2 (GND), U2.2 (GND), U3.1 (AGND), U3.16 (PGND), U4.A1 (GND), U4.A7 (GND), U4.A10 (GND), U4.A13 (GND), U4.A18 (GND), U4.B16 (GND), U4.C1 (GND), U4.E5 (GND), U4.E7 (GND), U4.E9 (GND), U4.E11 (GND), U4.E13 (GND), U4.E18 (GND), U4.F1 (GND), U4.F6 (GND), U4.F8 (GND), U4.F10 (GND), U4.F12 (GND), U4.F14 (GND), U4.G5 (GND), U4.G7 (GND), U4.G9 (GND), U4.G11 (GND), U4.G13 (GND), U4.H6 (GND), U4.H8 (GND), U4.H10 (GND), U4.H12 (GND), U4.H14 (GND), U4.H18 (GND), U4.J1 (GND), U4.J5 (GND), U4.J7 (GND), U4.J9 (GND), U4.J11 (GND), U4.J13 (GND), U4.K6 (GND), U4.K8 (GND), U4.K10 (GND), U4.K12 (GND), U4.K14 (GND), U4.L5 (GND), U4.L7 (GND), U4.L9 (GND), U4.L11 (GND), U4.L13 (GND), U4.L18 (GND), U4.M1 (GND), U4.M6 (GND), U4.M8 (GND), U4.M10 (GND), U4.M12 (GND), U4.M16 (GND), U4.N7 (GND), U4.N9 (GND), U4.N12 (GND), U4.N17 (GND), U4.P4 (GND), U4.P7 (GND), U4.P9 (GND), U4.R12 (GND), U4.R16 (GND), U4.T4 (GND), U4.T11 (GND), U4.T17 (GND), U4.U14 (GND), U4.U15 (GND), U4.V1 (GND), U4.V6 (GND), U4.V9 (GND), U4.V14 (GND), U4.V18 (GND), U5.2 (GND), U6.3 (GND), U7.4 (GND), U8.4 (GND), U9.4 (GND), U10.A1 (VSS), U10.A3 (VSSQ), U10.B7 (VSSQ), U10.C3 (VSSQ), U10.D7 (VSSQ), U10.E3 (VSS), U10.J1 (VSS), U14.29 (VSS), U14.49 (PAD_GND), X1.2 (GND), X2.3 (GND), Y1.2
unnamed: BTN1.1, BTN2.1, BTN3.1, R118.1
unnamed: C6.1, C8.1, L1.2, R3.1, R10.1, TP1.1
unnamed: C7.1, C9.1, L2.2, R5.1, R11.1, TP2.1
unnamed: C24.1, C29.1, L3.2, R17.1, R21.1, TP4.1
unnamed: C109.1, C112.1, FB1.1, U14.1 (AVDDH), U14.12 (AVDDH)
unnamed: C114.1, C116.1, FB2.2, U14.4 (AVDDL), U14.9 (AVDDL)
unnamed: D1.2 (A), R31.2
unnamed: D2.2 (A), R32.2
unnamed: D5.1 (K), R46.1
unnamed: D6.2 (A), R47.1
unnamed: D7.1 (K), R48.2
unnamed: D8.2 (A), R55.1
unnamed: J2.73, R128.2
unnamed: J2.75, R134.2
unnamed: J2.97, R138.2
unnamed: J2.100, R139.1
unnamed: J3.1, R14.1
unnamed: J3.3, R16.1
unnamed: J4.1, R40.2
unnamed: J4.2, R41.2
unnamed: J4.3, R42.2
unnamed: J4.4, R43.2
unnamed: R7.1, U4.U16 (GND)
unnamed: R8.1, U4.V16 (GND)
unnamed: R3.2, R4.1, U1.5 (FB)
unnamed: L1.1, U1.3 (SW)
unnamed: R5.2, R6.1, U2.5 (FB)
unnamed: L2.1, U2.3 (SW)
unnamed: R1.2, R2.1, U3.4 (EN)
unnamed: R12.2, R14.2, R15.2, R16.2, U3.2 (FB)
unnamed: C10.1, R13.1, R15.1, TP3.1, U3.3 (OUT_S), U3.8 (OUT), U3.9 (OUT), U3.10 (OUT)
unnamed: U3.5 (SW), U3.6 (SW), U3.7 (SW), U3.15 (SW)
unnamed: R109.2, U4.V12 (SER_RTERM)
unnamed: TP12.1, U4.R4 (IO_WA_B5/SPI_FWD)
unnamed: R9.1, U4.N16 (NC)
unnamed: R17.2, R18.1, U5.5 (FB)
unnamed: L3.1, U5.3 (SW)
unnamed: U6.4 (Y), U7.1 (1A)
unnamed: U7.2 (1B), U7.3 (2Y)
unnamed: R31.1, U7.5 (2A), U7.7 (1Y)
unnamed: U8.2 (1B), U8.3 (2Y)
unnamed: R32.1, U8.5 (2A), U8.7 (1Y)
unnamed: R37.2, U9.6 (SCLK)
unnamed: C115.1, C117.1, C119.1, FB3.2, U14.44 (AVDDL_PLL)
unnamed: R103.2, U14.48 (ISET)
unnamed: R143.2, X2.1 (OE)
PWR_BTN: J2.92, U4.G18 (IO_EA_A7)
RST_N: C138.1, J2.72, J2.99, R111.2, U4.N15 (IO_SB_B8), U4.T15 (RST_N), U7.6 (2B), U8.6 (2B)
SDRAM_A0: U4.H4 (IO_WB_B8), U10.H7 (A0)
SDRAM_A1: U4.A3 (IO_NA_A0), U10.H8 (A1)
SDRAM_A2: U4.B3 (IO_NA_B0), U10.J8 (A2)
SDRAM_A3: U4.M3 (IO_WB_A1), U10.J7 (A3)
SDRAM_A4: U4.B2 (IO_WC_B8), U10.J3 (A4)
SDRAM_A5: U4.C4 (IO_WC_B7), U10.J2 (A5)
SDRAM_A6: U4.H2 (IO_WB_B7), U10.H3 (A6)
SDRAM_A7: U4.D4 (IO_WC_B6), U10.H2 (A7)
SDRAM_A8: U4.C3 (IO_WC_A7), U10.H1 (A8)
SDRAM_A9: U4.G2 (IO_WC_B0), U10.G3 (A9)
SDRAM_A10: U4.B4 (IO_NA_B1), U10.H9 (A10)
SDRAM_A11: U4.G1 (IO_WC_A0), U10.G2 (A11)
SDRAM_A12: U4.B1 (IO_WC_A8), U10.G1 (A12)
SDRAM_BA0: U4.H1 (IO_WB_A7), U10.G7 (BA0)
SDRAM_BA1: U4.H3 (IO_WB_A8), U10.G8 (BA1)
SDRAM_CKE: U4.G4 (IO_WC_B1), U10.F3 (CKE)
SDRAM_CLK: U4.G3 (IO_WC_A1), U10.F2 (CLK)
SDRAM_D0: U4.K4 (IO_WB_B4), U10.A8 (DQ0)
SDRAM_D1: U4.L4 (IO_WB_B2), U10.B9 (DQ1)
SDRAM_D2: U4.K3 (IO_WB_A4), U10.B8 (DQ2)
SDRAM_D3: U4.L3 (IO_WB_A2), U10.C9 (DQ3)
SDRAM_D4: U4.K1 (IO_WB_A5), U10.C8 (DQ4)
SDRAM_D5: U4.K2 (IO_WB_B5), U10.D9 (DQ5)
SDRAM_D6: U4.M4 (IO_WB_B1), U10.D8 (DQ6)
SDRAM_D7: U4.L2 (IO_WB_B3), U10.E9 (DQ7)
SDRAM_D8: U4.D3 (IO_WC_A6), U10.E1 (DQ8)
SDRAM_D9: U4.E4 (IO_WC_B4), U10.D2 (DQ9)
SDRAM_D10: U4.D1 (IO_WC_A5), U10.D1 (DQ10)
SDRAM_D11: U4.E3 (IO_WC_A4), U10.C2 (DQ11)
SDRAM_D12: U4.E2 (IO_WC_B3), U10.C1 (DQ12)
SDRAM_D13: U4.F4 (IO_WC_B2), U10.B2 (DQ13)
SDRAM_D14: U4.F3 (IO_WC_A2), U10.B1 (DQ14)
SDRAM_D15: U4.E1 (IO_WC_A3), U10.A2 (DQ15)
SDRAM_DQM0: U4.L1 (IO_WB_A3), U10.E8 (DQML)
SDRAM_DQM1: U4.D2 (IO_WC_B5), U10.F1 (DQMH)
SDRAM_VCC: C57.1, C58.1, C75.1, C76.1, C77.1, C78.1, C79.1, C80.1, C86.1, C87.1, C88.1, C89.1, C90.1, C91.1, C92.1, C93.1, R115.1, R116.1, U4.A2 (VDD_WC), U4.A5 (VDD_NA), U4.B7 (VDD_NA), U4.B10 (VDD_NB), U4.B13 (VDD_NB), U4.C2 (VDD_WC), U4.D5 (VDD_WC), U4.E6 (VDD_NA), U4.E8 (VDD_NA), U4.E10 (VDD_NB), U4.E12 (VDD_NB), U4.F2 (VDD_WC), U4.F5 (VDD_WC), U4.F7 (VDD_NA), U4.F11 (VDD_NB), U4.H5 (VDD_WB), U4.J2 (VDD_WB), U4.K5 (VDD_WB), U4.M2 (VDD_WB), U4.M5 (VDD_WB), U10.A7 (VDDQ), U10.A9 (VDD), U10.B3 (VDDQ), U10.C7 (VDDQ), U10.D3 (VDDQ), U10.E7 (VDD), U10.J9 (VDD)
SDRAM_nCAS: U4.J4 (IO_WB_B6), U10.F7 (~CAS)
SDRAM_nCS: U4.N1 (IO_WB_A0), U10.G9 (~CS)
SDRAM_nRAS: U4.J3 (IO_WB_A6), U10.F8 (~RAS)
SDRAM_nWE: U4.N2 (IO_WB_B0), U10.F9 (~WE)
VDD_CLK: C4.2, C47.1, C48.1, C56.1, C98.1, C100.1, C102.1, C103.1, C105.1, C107.1, C110.1, C126.1, C131.1, C132.1, J2.88, J2.90, J4.5, JP1.1 (A), Q1.1 (G), Q2.1 (G), R10.2, R33.1, R34.1, R35.1, R36.1, R38.1, R66.1, R67.1, R70.1, R71.1, R72.1, R73.1, R96.1, R111.1, R112.1, R116.2, R122.2, R123.2, R143.1, R144.1, R145.1, R146.1, SW1.1, SW1.2, U4.A16 (VDD_EB), U4.B18 (VDD_EB), U4.E14 (VDD_EB), U4.E17 (VDD_EB), U4.F13 (VDD_EB), U4.T14 (VDD_CLK), U6.6 (VCC), U7.8 (VCC), U8.8 (VCC), U9.8 (VCC), U14.16 (DVDDH), U14.34 (DVDDH), U14.40 (DVDDH), X2.6 (VDD), Y1.1, Y1.4
VDD_CORE: C13.1, C14.1, C15.1, C16.1, C17.1, C18.1, C21.1, C22.1, C23.1, C26.1, C27.1, C28.1, C31.1, C32.1, C33.1, C34.1, C35.1, C36.1, C37.1, C38.1, C39.1, C40.1, C41.1, C120.1, C121.1, C122.1, C123.1, C124.1, C125.1, R13.2, R23.1, R105.1, R106.1, U4.F9 (VDD), U4.G6 (VDD), U4.G8 (VDD), U4.G10 (VDD), U4.G12 (VDD), U4.H7 (VDD), U4.H9 (VDD), U4.H11 (VDD), U4.H13 (VDD), U4.J6 (VDD), U4.J8 (VDD), U4.J10 (VDD), U4.J12 (VDD), U4.K7 (VDD), U4.K9 (VDD), U4.K11 (VDD), U4.K13 (VDD), U4.L6 (VDD), U4.L8 (VDD), U4.L10 (VDD), U4.L12 (VDD), U4.M7 (VDD), U4.M9 (VDD), U4.M11 (VDD), U4.M13 (VDD), U4.N6 (VDD), U4.N8 (VDD), U4.N10 (VDD)
VDD_PLL: C42.1, R23.2, TP6.1, U4.P16 (VDD_PLL)
VDD_SER: C128.1, R9.2, R106.2, TP10.1, U4.U12 (VDD_SER), U4.V17 (VDD_SER)
VDD_SER_PLL: C127.1, R105.2, TP8.1, U4.T16 (VDD_SER_PLL)

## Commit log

2026-01-04 initial commit, not jet structured
2026-01-04 changed pcb
2026-01-05 changes to DE10 schematic (GPIO)
2026-01-06 Code from Sven Krause added
2026-01-06 changed PCB pinout
2026-01-06 changed minor pin fixes
2026-01-06 changed initial pcb layout
2026-01-09 final v1 PCB design. Missing via stitching
2026-01-09 uplead ready to order PCBs
2026-01-10 Data flow csi_top and cci_handler created
2026-01-10 csi_rx_top diagramm added
2026-01-10 color added to diagrams
2026-01-10 Colors added to diagrams
2026-01-11 Diagram for video_output_ctrl added
2026-01-19 ulxtm 3D file
2026-01-19 schem for new toplevel added
2026-01-19 First test code added
2026-01-20 step
2026-01-26 basic ESY project structure added
2026-01-29 ibom added
2026-01-29 USER LEDs added to firmware
2026-01-29 Place and route added
2026-01-29 Aehm, ja
2026-02-02 Simple HW test created
2026-02-03 Shellscript for FPGA programming added
2026-02-05 ignored mac specific storage files
2026-02-05 Added software reset and disabled defect correction.
2026-02-05 Set analogue gain to 0
2026-02-05 Disabled digital gain
2026-02-05 Corrected formatting
2026-02-05 Registeradresse korrigiert
2026-02-05 disabled black pixel correction by setting pedestal to 0
2026-02-10 First running firmware
2026-02-10 Changed output to RAW10
2026-02-10 fixed bug and adjusted resolution to be full sensor instead of crop.
2026-02-10 Code von Sven Krause angepasst
2026-03-03 Added dsstore files to gitignore
2026-03-03 Fix usbipd typo
2026-03-03 Format
2026-03-03 Remove code for button handling
2026-03-03 Knight rider attempt #1
2026-03-03 Added script for simplified synthesis and execution.
2026-03-03 Corrected relevant led assigning
2026-03-17 project files added
2026-03-17 signals corrected in DE10.v
2026-03-20 cleanup
2026-03-20 Add mechanical design files

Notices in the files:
parts and their libraries:
COPYRIGHT: Copyright (C) 2022 Ultra Librarian. All rights reserved.
project_license: CERN-OHL-S v2
